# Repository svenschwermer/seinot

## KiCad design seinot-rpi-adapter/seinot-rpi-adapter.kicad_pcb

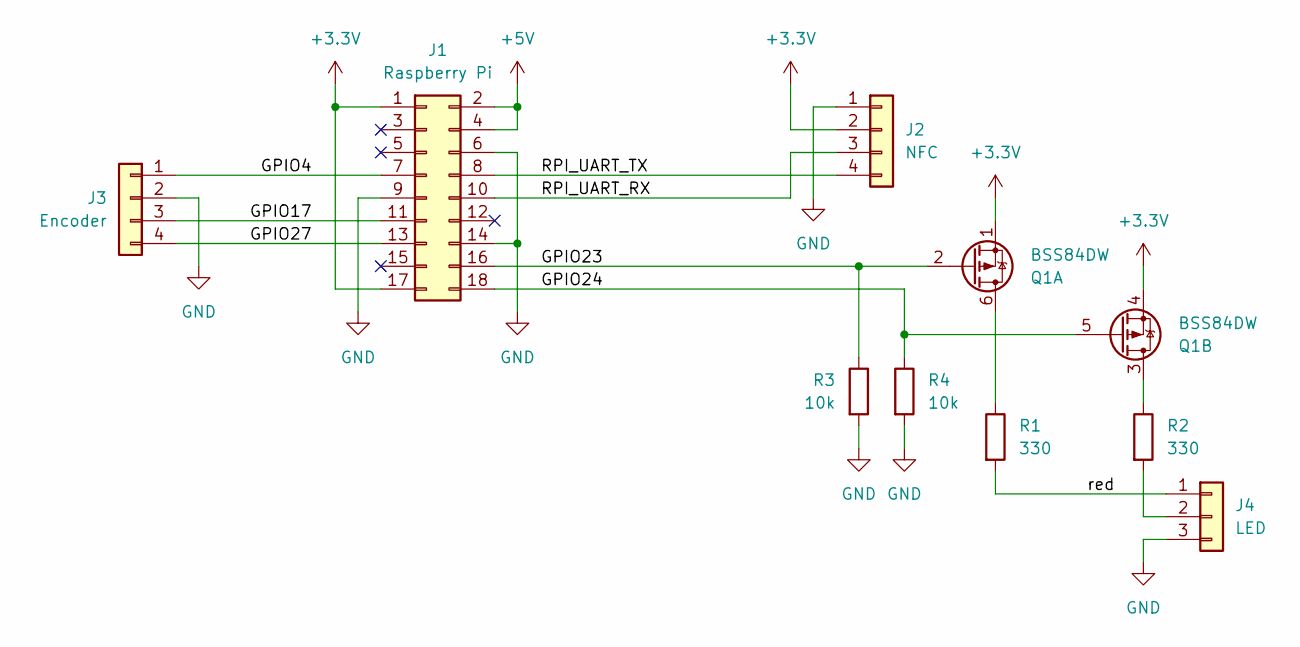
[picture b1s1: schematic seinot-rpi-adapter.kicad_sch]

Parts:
J1: Raspberry Pi; PinSocket_2x09_P2.54mm_Vertical
J2: NFC; PinHeader_1x04_P2.54mm_Horizontal
J3: Encoder; PinHeader_1x04_P2.54mm_Horizontal
J4: LED; PinHeader_1x03_P2.54mm_Horizontal
Q1: BSS84DW; SOT-363_SC-70-6_Handsoldering
R1, R2: 330; R_0805_2012Metric_Pad1.20x1.40mm_HandSolder
R3, R4: 10k; R_0805_2012Metric_Pad1.20x1.40mm_HandSolder

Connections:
+3.3V: J1.1, J1.17, J2.2, Q1.1 (S), Q1.4 (S)
+5V: J1.2, J1.4
/GPIO4: J1.7, J3.1
/GPIO17: J1.11, J3.3
/GPIO23: J1.16, Q1.2 (G), R3.1
/GPIO24: J1.18, Q1.5 (G), R4.1
/GPIO27: J1.13, J3.4
/RPI_UART_RX: J1.10, J2.3
/RPI_UART_TX: J1.8, J2.4
GND: J1.6, J1.9, J1.14, J2.1, J3.2, J4.3, R3.2, R4.2
unnamed: J4.1, R1.2
unnamed: J4.2, R2.2
unnamed: Q1.6 (D), R1.1
unnamed: Q1.3 (D), R2.1

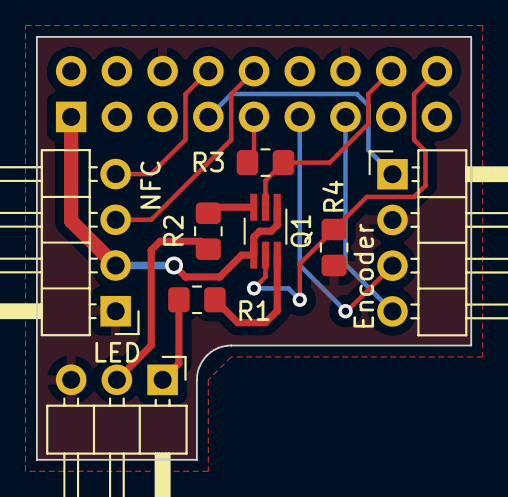
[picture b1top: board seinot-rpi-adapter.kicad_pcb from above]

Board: 2 copper layers, 24.1 x 23.5 mm, 9 parts (1 on the bottom side), 14 nets.

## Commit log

2023-10-06 Add panel++
2023-10-11 Add cartridge drawing
2023-10-14 panel: Create unified SVG
2023-10-15 panel: Remove fill of non-closed paths
2023-10-16 panel: 1st print attempt
    material: medium aspen hardwood
    hd engraving
2023-11-20 Add cartridges
2023-11-21 add laser settings
2023-11-21 cartridge: flip magnet circles
2024-01-04 Add elsa cartridge
2024-02-19 booting rpi zero w
2024-06-24 Yocto-based OS working
2024-06-26 Make volume control configurable
2024-06-26 Add utility to configure wifi
2024-06-30 dropbear: Add public key
2024-06-30 seinot: Adjust volume settings
2024-09-07 Add Kardemomme and Hakkebakke
2024-09-07 Remove openwrt submodule
2024-09-07 Add docs
2024-09-07 Add RPi adapter PCB
2024-12-09 Add sabeltann/fisk+brokkoli
